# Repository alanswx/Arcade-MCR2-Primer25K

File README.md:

# Bally Midway MCR2 Arcade Core for Gowin Tang FPGAs

Standalone port of the Bally Midway MCR-2 arcade hardware (Tron, Domino
Man, Satan's Hollow, Wacko, Kozmik Kroozr, Two Tigers) for Sipeed Tang
FPGA boards — no MiSTer/HPS required. The flagship target is the **Tang
Console 60K**: all six games in one bitstream, selected at runtime from an
on-screen menu, with ROMs loaded from a microSD card.

| Board | Status |
|---|---|
| **Tang Console 60K** (GW5AT-60) | All six games + OSD menu; 720p HDMI with audio (DDR3 framebuffer); analog RGB at 31/15 kHz for real cabinets; USB gamepad; SD ROM loading |
| Tang Primer 25K (GW5A-25) | Domino Man over HDMI (single game per build, BSRAM-limited) |
| Tang Console 138K (GW5AST-138) | Stale — needs the 60K backport |

New here? Read [handoff_v4_60k_multicore.md](handoff_v4_60k_multicore.md)
for the current platform state and family runway.

Deeper docs: build gotchas and architecture notes in [CLAUDE.md](CLAUDE.md),
open issues in [TODO.md](TODO.md), bench hookup in
[docs/bench_wiring.md](docs/bench_wiring.md), cabinet shield spec in
[docs/universal_mcr_shield_spec.md](docs/universal_mcr_shield_spec.md),
porting plan for the other MCR generations in
[docs/mcr_core_roadmap.md](docs/mcr_core_roadmap.md).

---

## 1. Generate the ROM hex tables

ROM zips (MAME sets) go in `roms/` — they are **not** in the repo. Then,
from the repo root:

```sh
python3 tools/merge_roms.py tron     # or domino / shollow / wacko / kroozr / twotiger
```

This writes the `rom_*.hex` tables the build bakes into BSRAM and sets the
board's `game_config.vh`. On the 60K the baked game only decides **what
boots with no SD card** — every game is reachable at runtime from the OSD.

## 2. Build

Headless (recommended; macOS paths shown — see CLAUDE.md for why the IDE
flow needs extra care):

```sh
GWLIB=/Applications/GowinIDE.app/Contents/Resources/Gowin_EDA/IDE/lib
GW=/Applications/GowinIDE.app/Contents/Resources/Gowin_EDA/IDE/bin/gw_sh
cd mcr2_console60k
DYLD_LIBRARY_PATH="$GWLIB" DYLD_FRAMEWORK_PATH="$GWLIB" "$GW" build.tcl
```

The bitstream lands at `mcr2_console60k/impl/pnr/mcr2_console60k.fs`.
Prebuilt images for all six games are kept in `bitstreams/`.

IDE builds work too (open `mcr2_console60k/mcr2_console60k.gprj`, Run All)
but several project settings must be exactly right — read the Gotchas
table in CLAUDE.md first; in particular **Place & Route → Place Option
must be 2** or HDMI silently dies.

## 3. Flash the board

With [openFPGALoader](https://github.com/trabucayre/openFPGALoader)
(`brew install openfpgaloader`), board connected over USB-C:

```sh
# quick test - loads SRAM, lost at power-off
openFPGALoader -b tangconsole bitstreams/console60k_tron.fs

# make it the POWER-ON default - writes the SPI flash
openFPGALoader -b tangconsole -f bitstreams/console60k_tron.fs
```

The `-f` form replaces whatever was in flash (e.g. NESTang) — reflash that
the same way if you want it back. The Gowin Programmer GUI works as well
(External Flash Mode → exFlash Erase, Program).

## 4. Make the SD card (all six games, switchable from the menu)

The ROM pack lives in **raw sectors starting at sector 2048** (1 MiB in) —
no filesystem involved, and it coexists with a normally-formatted card
(standard SD formatting starts the first partition at 4 MiB+; existing
files are untouched).

```sh
python3 tools/make_rompack.py                 # builds mcr_rompack.img from roms/
sudo python3 tools/write_rompack.py           # lists candidate cards
sudo python3 tools/write_rompack.py disk4     # writes + verifies (macOS)
```

`write_rompack.py` refuses to touch anything that is not a removable disk,
refuses cards whose partitions would overlap the pack, and verifies the
header after writing. On Linux/Windows use the `dd`/Win32DiskImager recipe
that `make_rompack.py` prints.

Put the card in the **console's** microSD slot. Every game you select in
the OSD is saved to the card (a reserved sector below the pack), and the
next power-on boots straight back into it - so a cabinet owner picks a
game once and it sticks. With no card (or a blank prefs sector) the
baked-in game boots.

## 5. Play

- **USB gamepad** in the left USB-A port: D-pad = joystick, A = Button 1,
  Start = Start 1, Select = Coin 1 (B/X/Y vary per game — see the input
  maps in `mcr2_console60k_top.sv`).
- **Select+Start opens the game-select menu** on every video output:
  Up/Down move, A loads the highlighted game from the SD card, B exits.
  The screen freezing (HDMI) or dropping sync (analog) for ~1 s after
  pressing A is the ROM reload, not a crash.
- Board keys: AA13 = reset, AB13 = Coin 1.
- HDMI is always live at 720p. Analog RGB comes out of the J10 header
  (31 kHz VGA, or jumper J10-37 to GND for native 15 kHz arcade timing) —
  wiring recipes in [docs/bench_wiring.md](docs/bench_wiring.md).
- A UART status beacon prints on the USB-C serial port (115200 8N1) for
  case-closed debugging — field decoding in docs/bench_wiring.md.

## 6. Cabinet integration

The goal is a drop-in board for real MCR cabinets: analog 15 kHz RGB,
original harness connectors, physical DIPs for game options. For anyone
building the PCB: the **frozen 40-pin header sheet is
[docs/shield_j10_pinout.md](docs/shield_j10_pinout.md)** — one header
carries video, audio and all controls (inputs via a 74HC165 chain that
covers every game, outputs via 74HC595). The consolidated electrical spec
is [docs/universal_mcr_shield_spec.md](docs/universal_mcr_shield_spec.md);
per-game harness pinouts are in
[docs/mcr_game_input_matrix.md](docs/mcr_game_input_matrix.md).

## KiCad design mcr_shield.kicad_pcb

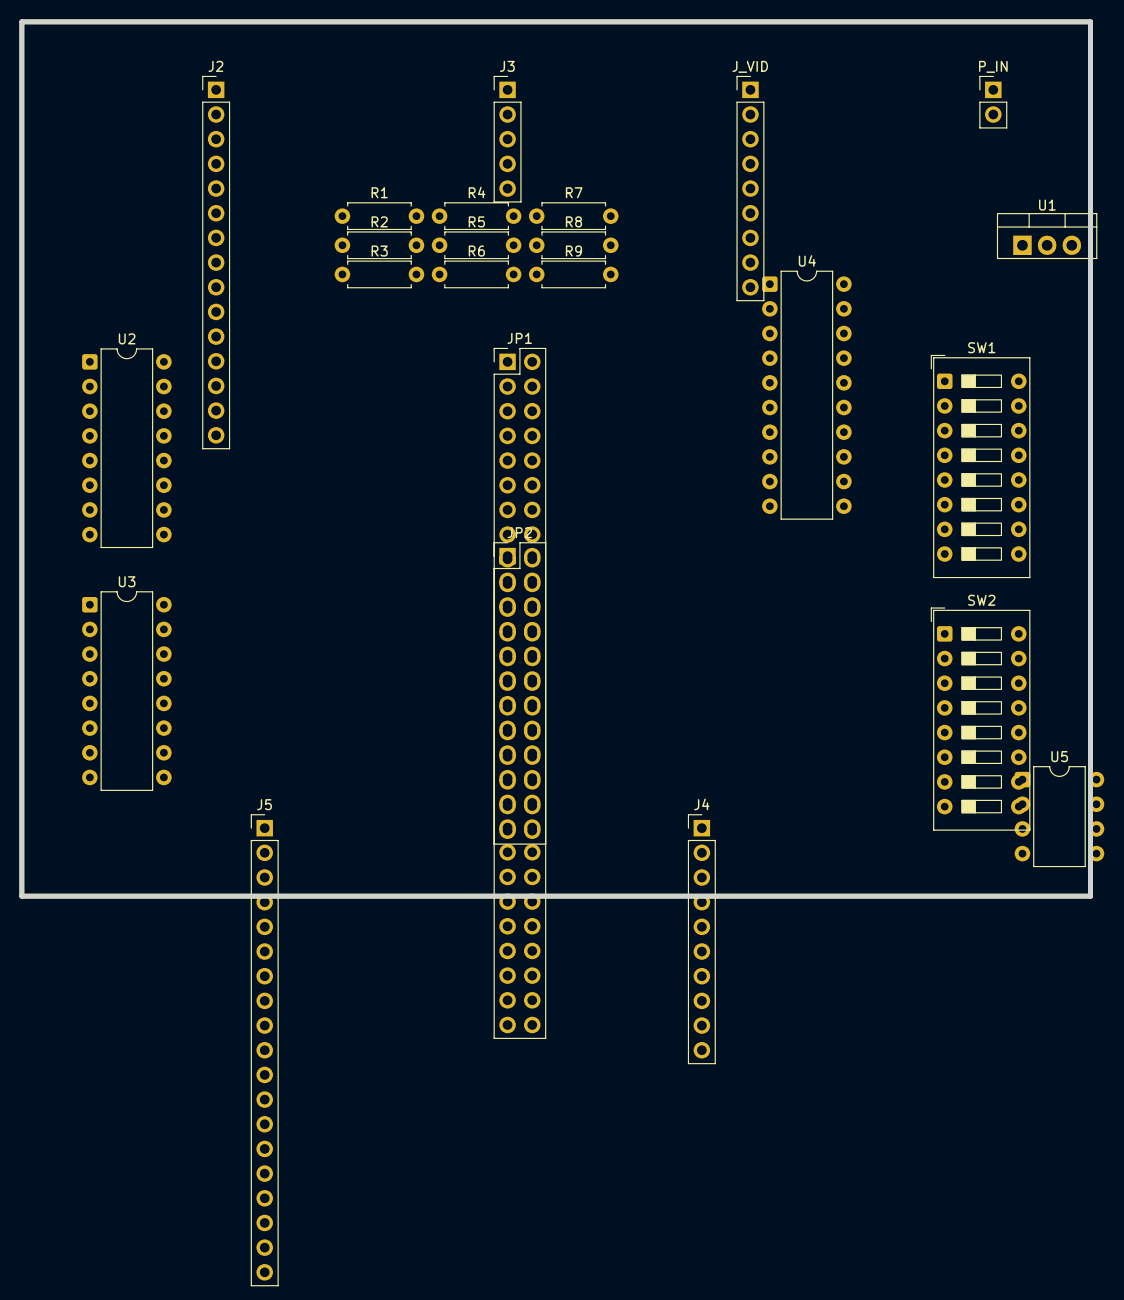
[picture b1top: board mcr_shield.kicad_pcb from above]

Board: 2 copper layers, 110.0 x 90.0 mm, 24 parts (0 on the bottom side), 43 nets, no tracks yet.

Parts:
J2: MCR_P1_Controls; PinHeader_1x15_P2.54mm_Vertical
J3: MCR_System_Coin; PinHeader_1x05_P2.54mm_Vertical
J4: MCR_Opt_X_Dial; PinHeader_1x10_P2.54mm_Vertical
J5: MCR_P2_Controls; PinHeader_1x19_P2.54mm_Vertical
JP1: Tang_2x20_H1; PinHeader_2x20_P2.54mm_Vertical
JP2: Tang_2x20_H2; PinHeader_2x20_P2.54mm_Vertical
J_VID: MCR_Video_Out; PinHeader_1x09_P2.54mm_Vertical
P_IN: Power_+12V_GND; PinHeader_1x02_P2.54mm_Vertical
R1: 3.9k_Red_LSB; R_Axial_DIN0207_L6.3mm_D2.5mm_P7.62mm_Horizontal
R2: 2.0k_Red_Mid; R_Axial_DIN0207_L6.3mm_D2.5mm_P7.62mm_Horizontal
R3: 1.0k_Red_MSB; R_Axial_DIN0207_L6.3mm_D2.5mm_P7.62mm_Horizontal
R4: 3.9k_Green_LSB; R_Axial_DIN0207_L6.3mm_D2.5mm_P7.62mm_Horizontal
R5: 2.0k_Green_Mid; R_Axial_DIN0207_L6.3mm_D2.5mm_P7.62mm_Horizontal
R6: 1.0k_Green_MSB; R_Axial_DIN0207_L6.3mm_D2.5mm_P7.62mm_Horizontal
R7: 3.9k_Blue_LSB; R_Axial_DIN0207_L6.3mm_D2.5mm_P7.62mm_Horizontal
R8: 2.0k_Blue_Mid; R_Axial_DIN0207_L6.3mm_D2.5mm_P7.62mm_Horizontal
R9: 1.0k_Blue_MSB; R_Axial_DIN0207_L6.3mm_D2.5mm_P7.62mm_Horizontal
SW1: Game_Selector; SW_DIP_SPSTx08_Slide_9.78x22.5mm_W7.62mm_P2.54mm
SW2: Cabinet_Options; SW_DIP_SPSTx08_Slide_9.78x22.5mm_W7.62mm_P2.54mm
U1: Buck_Regulator; TO-220-3_Vertical
U2: Optocoupler_P1; DIP-16_W7.62mm
U3: Optocoupler_Sys; DIP-16_W7.62mm
U4: Sync_Buffer; DIP-20_W7.62mm
U5: Audio_Amplifier; DIP-8_W7.62mm

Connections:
5V_REGULATED: JP1.40, U1.3
12V_POWER: P_IN.1, U1.1
BTN_FIRE: JP1.3, U2.12
BTN_LEFT: JP1.1, U2.16
BTN_RIGHT: JP1.2, U2.14
BTN_SHIELD: JP1.4, U2.10
CAB_BLUE: J_VID.5, R7.2, R8.2, R9.2
CAB_BTN_FIRE: J2.5, U2.5
CAB_BTN_LEFT: J2.1, U2.1
CAB_BTN_RIGHT: J2.2, U2.3
CAB_BTN_SHIELD: J2.6, U2.7
CAB_GREEN: J_VID.3, R4.2, R5.2, R6.2
CAB_HSYNC: J_VID.8, U4.18
CAB_RED: J_VID.1, R1.2, R2.2, R3.2
CAB_VSYNC: J_VID.9, U4.16
FPGA_B0: JP1.15, R7.1
FPGA_B1: JP1.16, R8.1
FPGA_B2: JP1.17, R9.1
FPGA_G0: JP1.12, R4.1
FPGA_G1: JP1.13, R5.1
FPGA_G2: JP1.14, R6.1
FPGA_HSYNC: JP1.18, U4.2
FPGA_R0: JP1.9, R1.1
FPGA_R1: JP1.10, R2.1
FPGA_R2: JP1.11, R3.1
FPGA_VSYNC: JP1.19, U4.4
GAME_OPT0: JP1.31, SW2.1
GAME_OPT1: JP1.32, SW2.2
GAME_OPT2: JP1.33, SW2.3
GAME_OPT3: JP1.34, SW2.4
GAME_OPT4: JP1.35, SW2.5
GAME_OPT5: JP1.36, SW2.6
GAME_OPT6: JP1.37, SW2.7
GAME_OPT7: JP1.38, SW2.8
GAME_SEL0: JP1.23, SW1.1
GAME_SEL1: JP1.24, SW1.2
GAME_SEL2: JP1.25, SW1.3
GAME_SEL3: JP1.26, SW1.4
GAME_SEL4: JP1.27, SW1.5
GAME_SEL5: JP1.28, SW1.6
GAME_SEL6: JP1.29, SW1.7
GAME_SEL7: JP1.30, SW1.8
GND: J2.13, J4.10, J_VID.2, J_VID.4, J_VID.6, P_IN.2, U1.2, U2.2, U2.4, U2.6, U2.8, U2.9, U2.11, U2.13, U2.15, U4.10, U5.4
